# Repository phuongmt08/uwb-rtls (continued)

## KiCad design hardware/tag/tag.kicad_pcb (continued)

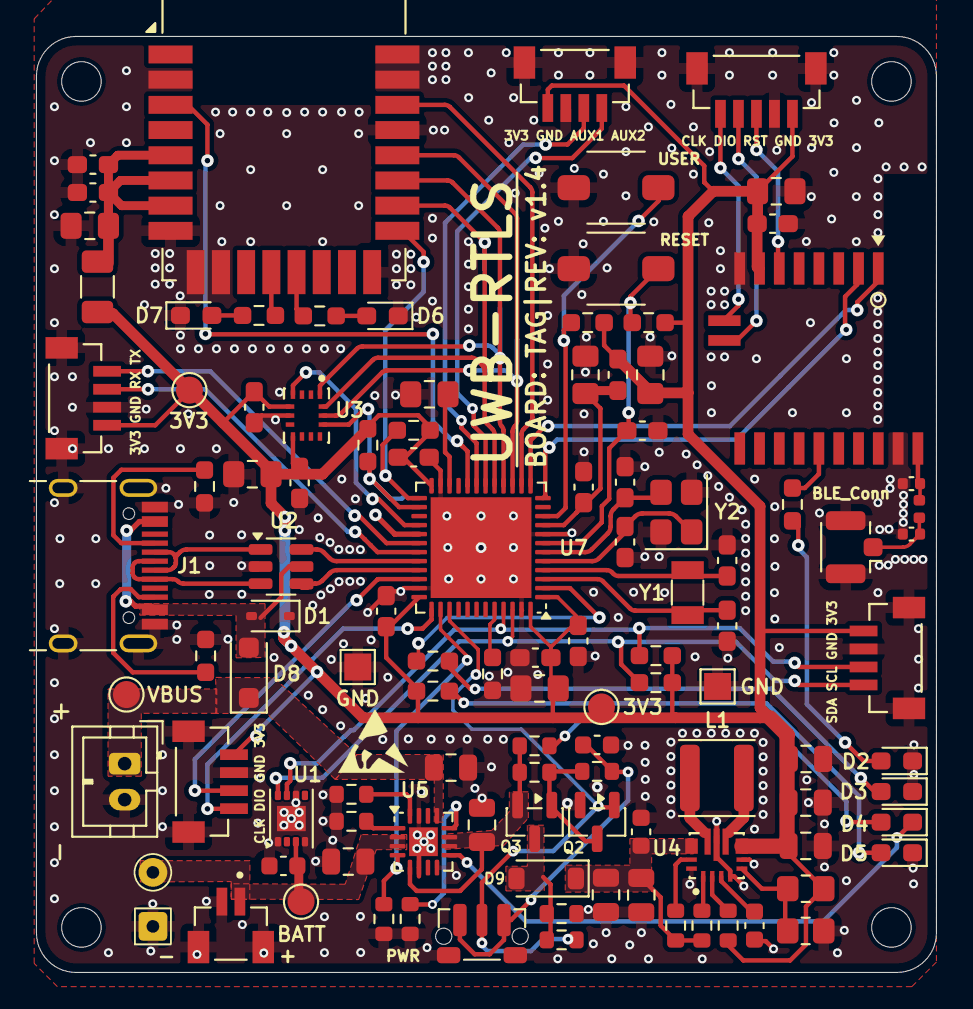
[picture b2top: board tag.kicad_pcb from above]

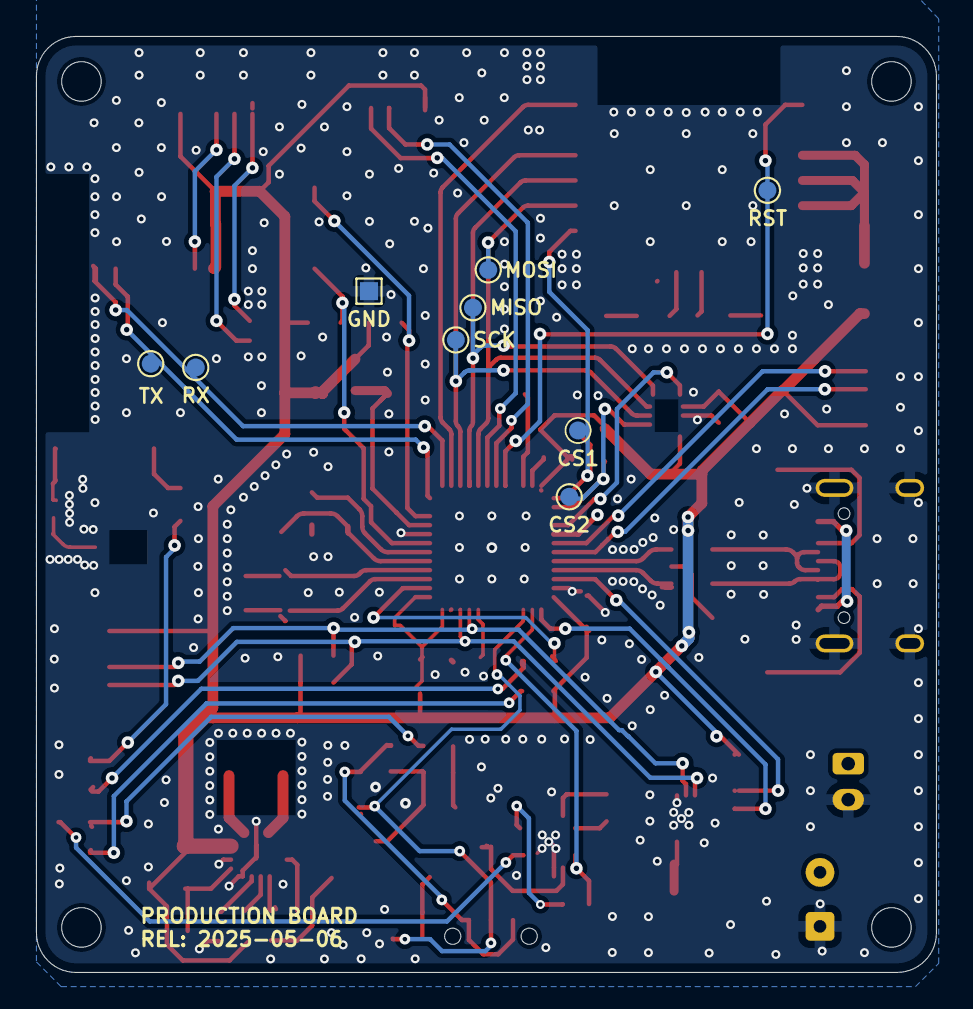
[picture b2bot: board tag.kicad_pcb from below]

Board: 2 copper layers, 50.0 x 52.0 mm, 121 parts (9 on the bottom side), 72 nets.

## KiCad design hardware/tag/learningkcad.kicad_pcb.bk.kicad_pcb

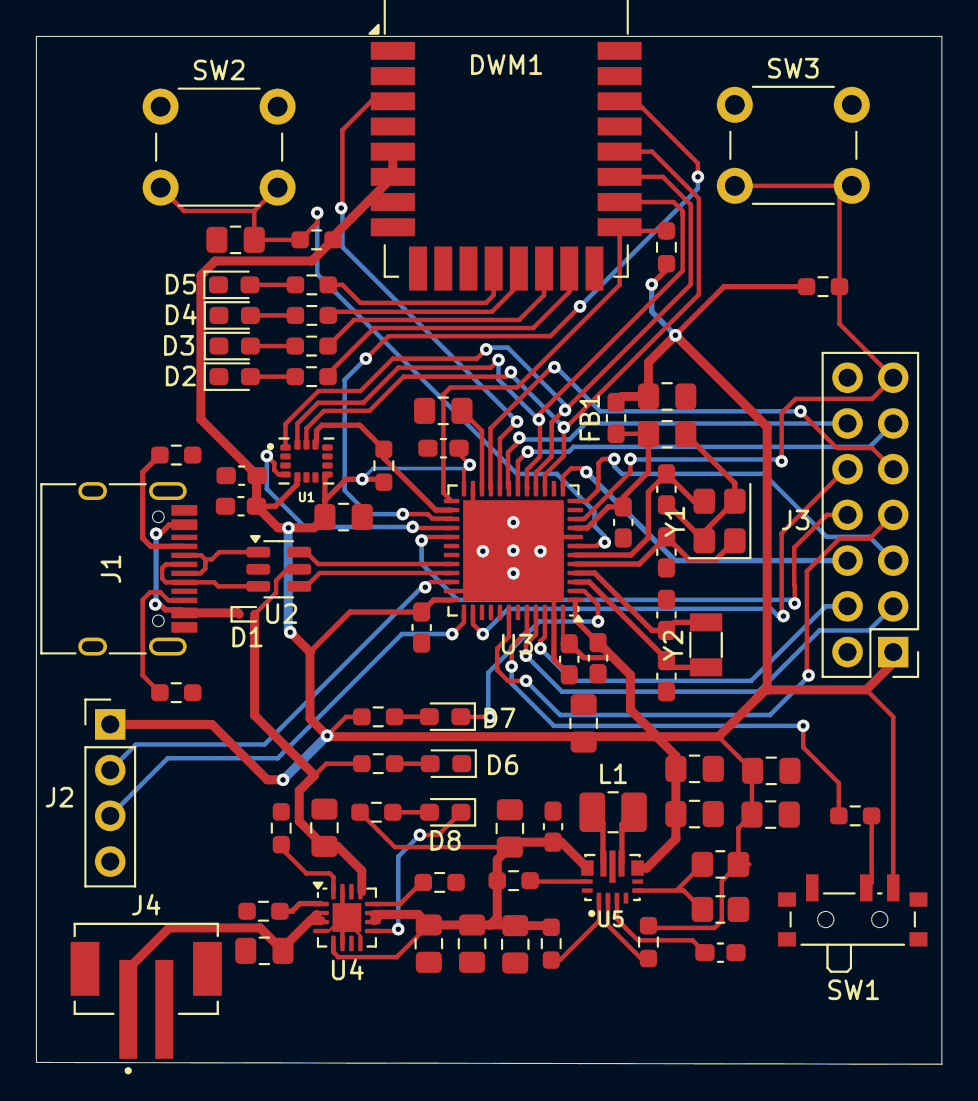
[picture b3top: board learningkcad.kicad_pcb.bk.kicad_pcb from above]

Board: 2 copper layers, 50.3 x 57.1 mm, 76 parts (0 on the bottom side), 65 nets.

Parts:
C1, C2, C5, C6, C7, C8, C9, C14, C18: 100n; C_0603_1608Metric_Pad1.08x0.95mm_HandSolder
C3, C13: 2.2u; C_0805_2012Metric_Pad1.18x1.45mm_HandSolder
C4, C15, C16, C17, C19: 10u; C_0805_2012Metric_Pad1.18x1.45mm_HandSolder
C10, C11, C23: 1u; C_0805_2012Metric_Pad1.18x1.45mm_HandSolder
C12: 100n; C_0805_2012Metric_Pad1.18x1.45mm_HandSolder
C20, C21, C22: 22u; C_0805_2012Metric_Pad1.18x1.45mm_HandSolder
C24, C25: 4.7u; C_0805_2012Metric_Pad1.18x1.45mm_HandSolder
CY1, CY2: 10p; C_0603_1608Metric_Pad1.08x0.95mm_HandSolder
CY3, CY4: 22p; C_0603_1608Metric_Pad1.08x0.95mm_HandSolder
D1: ESD9B5.0ST5G; D_SOD-923
D2, D3, D4, D5, D6, D7: LED; LED_0603_1608Metric_Pad1.05x0.95mm_HandSolder
D8: R; LED_0603_1608Metric_Pad1.05x0.95mm_HandSolder
DWM1: DWM1000
FB1: FerriteBead; L_0603_1608Metric_Pad1.05x0.95mm_HandSolder
J1: USB_C_Receptacle_USB2.0_16P; USB_C_Receptacle_HRO_TYPE-C-31-M-12
J2: Conn_01x04_Pin; PinHeader_1x04_P2.54mm_Vertical
J3: Conn_02x07_Odd_Even; PinHeader_2x07_P2.54mm_Vertical
J4: BATTERY; JST_B2B-PH-SM4-TB
L1: 1.5u; L_1008_2520Metric_Pad1.43x2.20mm_HandSolder
R1, R2, R7, R8, R9, R10, R14, R16, R17, R18: 10k; R_0603_1608Metric_Pad0.98x0.95mm_HandSolder
R3, R4, R11: 10K; R_0603_1608Metric_Pad0.98x0.95mm_HandSolder
R5, R6: 5k1; R_0603_1608Metric_Pad0.98x0.95mm_HandSolder
R12, R13: 4.7k; R_0603_1608Metric_Pad0.98x0.95mm_HandSolder
R15: 1.5k; R_0603_1608Metric_Pad0.98x0.95mm_HandSolder
R19: 3.1k; R_0603_1608Metric_Pad0.98x0.95mm_HandSolder
R20: 3.56k; R_0603_1608Metric_Pad0.98x0.95mm_HandSolder
R21: 470k; R_0805_2012Metric_Pad1.20x1.40mm_HandSolder
R22: 150k; R_0805_2012Metric_Pad1.20x1.40mm_HandSolder
SW1: SW_SPDT; SW_SPDT_PCM12
SW2, SW3: SW_Push; SW_PUSH_6mm_H9.5mm
U1: ICM-42688-P; PQFN50P300X250X97-14N
U2: USBLC6-2SC6 (DNP); SOT-23-6
U3: STM32F411CEUx; QFN-48-1EP_7x7mm_P0.5mm_EP5.6x5.6mm
U4: BQ24075RGT; VQFN-16-1EP_3x3mm_P0.5mm_EP1.6x1.6mm
U5: TPS63070RNMR; VREG_TPS63070RNMR
Y1: NX3225SA-24MHz; Crystal_SMD_3225-4Pin_3.2x2.5mm
Y2: NX3215SA-32.768kHz; Crystal_SMD_3215-2Pin_3.2x1.5mm

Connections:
+3.3V: C1.1, C2.1, C3.1, C4.1, C5.1, C6.1, C7.1, C8.1, C11.1, C19.1, C20.1, C21.1, C22.1, DWM1.5 (VDDAON), DWM1.6 (VDD3V3), DWM1.7 (VDD3V3), FB1.2, J2.1, J3.1, R1.1, R2.1, R3.2, R11.2, R13.2, R17.2, R21.1, SW1.3 (C), U1.5 (VDDIO), U1.8 (VDD), U3.1 (VBAT), U3.24 (VDD), U3.36 (VDD), U3.48 (VDD), U5.7_8 (VOUT)
+3.3VA: C9.1, C10.1, FB1.1, U3.9 (VDDA)
+BATT: C24.1, J4.1, U4.2 (BAT), U4.3 (BAT)
/FB: R21.2, R22.1, U5.5 (FB)
/IMU_INT: U1.4 (INT1/INT), U3.28 (PB15)
/LED_USR: D7.1 (K), U3.2 (PC13)
/PA0/BTN_USR: J3.13, R11.1, SW3.2, U3.10 (PA0)
/PA2 / USART2_TX: J3.5, U3.12 (PA2)
/PA3 / USART2_RX: J3.6, U3.13 (PA3)
/PA8 / TIM1_CH1: J3.8, U3.29 (PA8)
/PA15 / TIM2_CH1: J3.10, U3.38 (PA15)
/PB0 / ADC_IN8: J3.11, U3.18 (PB0)
/PB1 / ADC_IN9: J3.12, U3.19 (PB1)
/PB6 / TIM4_CH1: J3.7, U3.42 (PB6)
/PB8 / I2C1_SCL: J3.3, U3.45 (PB8)
/PB9 / I2C1_SDA: J3.4, U3.46 (PB9)
/PB10 / TIM2_CH3: J3.9, U3.21 (PB10)
/SPI_CS1: DWM1.17 (~SPICS), R2.2, U3.25 (PB12)
/SPI_CS2: R1.2, U1.12 (AP_CS), U3.26 (PB13)
/SPI_MISO: DWM1.19 (SPIMISO), U1.1 (AP_SDO/AP_AD0), U3.16 (PA6)
/SPI_MOSI: DWM1.18 (SPIMOSI), U1.14 (AP_SDA/AP_SDIO/AP_SDI), U3.17 (PA7)
/SPI_SCK: DWM1.20 (SPICLK), U1.13 (AP_SCL/AP_SCLK), U3.15 (PA5)
/SWDCLK: J2.3, U3.37 (PA14)
/SWDIO: J2.2, U3.34 (PA13)
/SYS: C15.1, C16.1, C17.1, C18.1, C25.1, R15.1, R16.2, R18.2, U4.5 (EN2), U4.10 (OUT), U4.11 (OUT), U5.12_13 (VIN)
/USB_OTG_DM: U2.6 (I/O1), U3.32 (PA11)
/USB_OTG_DP: U2.4 (I/O2), U3.33 (PA12)
/UWB_IQR: DWM1.22 (IRQ/GPIO8), U3.27 (PB14)
/UWB_LED_RX: DWM1.13 (GPIO2/RXLED), R9.2
/UWB_LED_RXOK: DWM1.15 (GPIO0/RXOKLED), R7.2
/UWB_LED_SDF: DWM1.14 (GPIO1/SFDLED), R8.2
/UWB_LED_TX: DWM1.12 (GPIO3/TXLED), R10.2
/UWB_RST: DWM1.3 (~RST), U3.20 (PB2)
GND: C1.2, C2.2, C3.2, C4.2, C5.2, C6.2, C7.2, C8.2, C9.2, C10.2, C11.2, C12.2, C13.2, C14.2, C15.2, C16.2, C17.2, C18.2, C19.2, C20.2, C21.2, C22.2, C23.1, C24.2, C25.2, CY1.1, CY2.1, CY3.1, CY4.1, D2.1 (K), D3.1 (K), D4.1 (K), D5.1 (K), D6.1 (K), DWM1.2 (WAKEUP), DWM1.8 (VSS), DWM1.9 (GPIO6/EXTRXE/SPIHA), DWM1.10 (GPIO5/EXTTXE/SPIPOL), DWM1.16 (VSS), DWM1.21 (VSS), DWM1.23 (VSS), DWM1.24 (VSS), J1.A1 (GND), J1.A12 (GND), J1.B1 (GND), J1.B12 (GND), J1.S1 (SHIELD), J2.4, J3.2, J3.14, J4.2, R5.1, R6.1, R14.1, R19.2, R20.2, R22.2, SW1.1 (A), SW2.1, SW3.1, U1.6 (GND), U1.7 (RESV_7), U1.11 (RESV_11), U2.2 (GND), U3.8 (VSSA), U3.23 (VSS), U3.35 (VSS), U3.47 (VSS), U3.49 (VSS), U4.4 (~CE), U4.6 (EN1), U4.8 (VSS), U4.15 (SYSOFF), U4.17 (VSS), U5.4 (GND), U5.6 (FB2), U5.10 (PGND), U5.15 (VSEL), Y1.2, Y1.4
unnamed: D1.1 (A1), J1.A4 (VBUS), J1.A9 (VBUS), J1.B4 (VBUS), J1.B9 (VBUS)
unnamed: D2.2 (A), R7.1
unnamed: D3.2 (A), R8.1
unnamed: D4.2 (A), R9.1
unnamed: D5.2 (A), R10.1
unnamed: D6.2 (A), R12.1
unnamed: D7.2 (A), R13.1
unnamed: D8.2 (A), R15.2
unnamed: D8.1 (K), U4.9 (~CHG)
unnamed: J1.A5 (CC1), R5.2
unnamed: J1.B5 (CC2), R6.2
unnamed: J1.A6 (D+), J1.B6 (D+), U2.3 (I/O2)
unnamed: J1.A7 (D-), J1.B7 (D-), U2.1 (I/O1)
unnamed: R4.1, SW1.2 (B)
unnamed: R4.2, U3.44 (BOOT0)
unnamed: C12.1, R3.1, SW2.2, U3.7 (NRST)
unnamed: CY3.2, U3.3 (PC14), Y2.2
unnamed: CY4.2, U3.4 (PC15), Y2.1
unnamed: CY1.2, U3.5 (PH0), Y1.1
unnamed: CY2.2, U3.6 (PH1), Y1.3
unnamed: C13.1, U3.22 (VCAP1)
unnamed: R19.1, U4.12 (ILIM)
unnamed: R20.1, U4.16 (ISET)
unnamed: R14.2, U4.1 (TS)
unnamed: R16.1, U5.14 (EN)
unnamed: L1.2, U5.11 (L1)
unnamed: L1.1, U5.9 (L2)
unnamed: R17.1, U5.2 (PG)
unnamed: R18.1, U5.1 (PS/SYNC)
unnamed: C14.1, U5.3 (VAUX)
VBUS: C23.2, D1.2 (A2), R12.2, U2.5 (VBUS), U4.13 (IN)

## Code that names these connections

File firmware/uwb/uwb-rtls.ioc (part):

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Mcu.Name=STM32F411C(C-E)Ux
Mcu.Package=UFQFPN48
Mcu.UserName=STM32F411CEUx
PA0-WKUP.GPIOParameters=GPIO_Label,GPIO_ModeDefaultEXTI
PA0-WKUP.GPIO_Label=BTN_USR
PA0-WKUP.GPIO_ModeDefaultEXTI=GPIO_MODE_IT_FALLING
PA0-WKUP.Signal=GPXTI0
PA10.Mode=Asynchronous
PA10.Signal=USART1_RX
PA11.Mode=Device_Only
PA11.Signal=USB_OTG_FS_DM
PA12.Mode=Device_Only
PA12.Signal=USB_OTG_FS_DP
PA13.Mode=Serial_Wire
PA13.Signal=SYS_JTMS-SWDIO
PA14.Mode=Serial_Wire
PA14.Signal=SYS_JTCK-SWCLK
PA2.GPIOParameters=GPIO_Label
PA2.GPIO_Label=UART2_BLE_TX
PA2.Mode=Asynchronous
PA2.Signal=USART2_TX
PA3.GPIOParameters=GPIO_Label
PA3.GPIO_Label=UART2_BLE_RX
PA3.Mode=Asynchronous
PA3.Signal=USART2_RX
PA4.GPIOParameters=GPIO_Label,GPIO_ModeDefaultEXTI
PA4.GPIO_Label=UWB_IRQ
PA4.GPIO_ModeDefaultEXTI=GPIO_MODE_IT_RISING
PA4.Signal=GPXTI4
PA5.Mode=Full_Duplex_Master
PA5.Signal=SPI1_SCK
PA6.Mode=Full_Duplex_Master
PA6.Signal=SPI1_MISO
PA7.Mode=Full_Duplex_Master
PA7.Signal=SPI1_MOSI
PA8.Signal=I2C3_SCL
PA9.Mode=Asynchronous
PA9.Signal=USART1_TX
PB0.GPIOParameters=GPIO_Label
PB0.GPIO_Label=AUX0
PB0.Signal=ADCx_IN8
PB1.GPIOParameters=GPIO_Label
PB1.GPIO_Label=AUX1
PB1.Signal=ADCx_IN9
PB12.GPIOParameters=GPIO_Speed,PinState,GPIO_PuPd,GPIO_Label
PB12.GPIO_Label=SPI1_CS1
PB12.GPIO_PuPd=GPIO_PULLUP
PB12.GPIO_Speed=GPIO_SPEED_FREQ_HIGH
PB12.PinState=GPIO_PIN_SET
PB12.Signal=GPIO_Output
PB13.GPIOParameters=GPIO_Speed,PinState,GPIO_Label
PB13.GPIO_Label=SPI1_CS2
PB13.GPIO_Speed=GPIO_SPEED_FREQ_HIGH
PB13.PinState=GPIO_PIN_SET
PB13.Signal=GPIO_Output
PB15.GPIOParameters=GPIO_Label
PB15.GPIO_Label=IMU_IRQ
PB15.Signal=GPXTI15
PB2.GPIOParameters=GPIO_PuPd,GPIO_Label
PB2.GPIO_Label=UWB_RST
PB2.GPIO_PuPd=GPIO_NOPULL
PB2.Signal=GPIO_Input
PB3.GPIOParameters=GPIO_PuPd,GPIO_Label
PB3.GPIO_Label=CHARGE_EN
PB3.GPIO_PuPd=GPIO_NOPULL
PB3.Signal=GPIO_Output
PB4.Signal=I2C3_SDA
PB5.GPIOParameters=GPIO_Label,GPIO_ModeDefaultEXTI
PB5.GPIO_Label=DIP1
PB5.GPIO_ModeDefaultEXTI=GPIO_MODE_IT_FALLING
PB5.Signal=GPXTI5
PB6.GPIOParameters=GPIO_Label,GPIO_ModeDefaultEXTI
PB6.GPIO_Label=DIP2
PB6.GPIO_ModeDefaultEXTI=GPIO_MODE_IT_FALLING
PB6.Signal=GPXTI6
PB7.GPIOParameters=GPIO_Label,GPIO_ModeDefaultEXTI
PB7.GPIO_Label=DIP3
PB7.GPIO_ModeDefaultEXTI=GPIO_MODE_IT_FALLING
PB7.Signal=GPXTI7
PB8.Mode=I2C
PB8.Signal=I2C1_SCL
PB9.Mode=I2C
PB9.Signal=I2C1_SDA
PC13-ANTI_TAMP.GPIOParameters=GPIO_Label
PC13-ANTI_TAMP.GPIO_Label=LED_USR
PC13-ANTI_TAMP.Signal=GPIO_Output
PC14-OSC32_IN.Signal=RCC_OSC32_IN
PC15-OSC32_OUT.Signal=RCC_OSC32_OUT
PH0\ -\ OSC_IN.Mode=HSE-External-Oscillator
PH0\ -\ OSC_IN.Signal=RCC_OSC_IN
PH1\ -\ OSC_OUT.Mode=HSE-External-Oscillator
PH1\ -\ OSC_OUT.Signal=RCC_OSC_OUT
RCC.HSE_VALUE=12000000
RCC.SYSCLKFreq_VALUE=96000000
RCC.SYSCLKSource=RCC_SYSCLKSOURCE_PLLCLK
board=custom

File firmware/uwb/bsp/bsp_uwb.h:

/**
 * @file       bsp_uwb.h
 * @copyright
 * @license
 * @version    0.4.0
 * @date       2025-12-11
 * @author     Phuong Mai
 * @brief      Board Support Package for UWB (DW1000)
 * @note       None
 * @example    None
 */
#ifndef __BSP_UWB_H
#define __BSP_UWB_H

/* Includes ----------------------------------------------------------- */
#include "common.h"
#include <stdbool.h>
#include "protos/protocol.pb.h"
#include "config.h"

#include "main.h"

typedef struct {
    uint16_t fp_amp1;
    uint16_t fp_amp2;
    uint16_t fp_amp3;
    uint16_t std_noise;
    uint16_t lde_threshold;
    uint16_t rx_pream_count;
    uint16_t fp_amp_norm_q8;
    uint16_t fp_snr_q8;
    uint16_t first_path_index_q6;
    uint16_t peak_path_index;
    uint16_t peak_path_amp;
    uint8_t  fp_confidence_q8;
    bool     confidence_valid;
    bool     valid;
} bsp_uwb_rx_quality_t;

typedef enum {
    BSP_UWB_EVENT_NONE = 0,
    BSP_UWB_EVENT_RX_OK,
    BSP_UWB_EVENT_RX_TIMEOUT,
    BSP_UWB_EVENT_RX_ERROR,
    BSP_UWB_EVENT_TX_DONE
} bsp_uwb_event_type_t;

typedef struct {
    bsp_uwb_event_type_t type;
    bool                 rx_windowed;
    uint16_t             rx_len;
    uint8_t              rx_data[128];
    uint64_t             rx_ts;
    uint64_t             tx_ts;
    bsp_uwb_rx_quality_t rx_quality;
} bsp_uwb_event_t;

/* Pin definitions (based on BU01 schematic) ------------------------- */
/* SPI pins - connected to SPI1 peripheral */
#define UWB_SPI_PORT        GPIOA
#define UWB_SCK_PIN         GPIO_PIN_5   /* PA5 - SPICLK (Pin 20) */
#define UWB_MISO_PIN        GPIO_PIN_6   /* PA6 - SPIMISO (Pin 19) */
#define UWB_MOSI_PIN        GPIO_PIN_7   /* PA7 - SPIMOSI (Pin 18) */
#ifdef UWB_CS_PORT
#undef UWB_CS_PORT
#endif
#ifdef UWB_CS_PIN
#undef UWB_CS_PIN
#endif
#define UWB_CS_PORT         SPI1_CS1_GPIO_Port
#define UWB_CS_PIN          SPI1_CS1_Pin  /* PB12 - SPICS (Pin 17) */

/* Control pins */
#ifdef UWB_RST_PORT
#undef UWB_RST_PORT
#endif
#ifdef UWB_RST_PIN
#undef UWB_RST_PIN
#endif
#define UWB_RST_PORT        UWB_RST_GPIO_Port
#define UWB_RST_PIN         UWB_RST_Pin   /* PB2 - RST (Pin 3) */
#define UWB_IRQ_PORT        UWB_IRQ_GPIO_Port
#define UWB_IRQ_PIN         UWB_IRQ_Pin   /* PA4 - IRQ/GPIO8 (Pin 22) */

/* Note: RX/TX LEDs are controlled by DW1000 GPIO2/GPIO3 directly, not STM32 */

/* Public function prototypes ----------------------------------------- */
/**
 * @brief Initialize DW1000 device
 * @return BSP_OK on success, BSP_ERR on failure
 */
bsp_err_t bsp_uwb_init(void);

/**
 * @brief  Check if UWB driver was successfully initialized.
 * @retval true if initialized, false otherwise
 */
bool bsp_uwb_is_initialized(void);

/**
 * @brief Configure UWB radio parameters from protobuf UWB config.
 * @param[in] cfg  Pointer to protobuf_uwb_cfg_t (sys_config.uwb)
 * @return BSP_OK on success, BSP_ERR on failure
 */
bsp_err_t bsp_uwb_configure(const protobuf_uwb_cfg_t *cfg);

/**
 * @brief Transmit a frame (blocking until complete)
 * @param[in] data   Frame data
 * @param[in] length Frame length in bytes
 * @return BSP_OK on success, BSP_ERR on failure
 */
bsp_err_t bsp_uwb_tx(const void *data, uint16_t length);

/**
 * @brief Non-blocking RX check - returns immediately
 * @param[out] data    Receive buffer
 * @param[in]  length  Maximum buffer size
 * @param[out] out_len Actual received length
 * @return BSP_OK if frame received, BSP_ERR if no frame or error
 * @note This function does NOT block. Returns immediately with status.
 */
bsp_err_t bsp_uwb_rx(void *data, uint16_t length, uint16_t *out_len);

/**
 * @brief Read 40-bit timestamp from DW1000 register
 * @param[in]  reg_addr  Register address (e.g., 0x15 for RX, 0x17 for TX)
 * @param[in]  sub_addr  Sub-address (usually 0x00)
 * @param[out] timestamp Pointer to store 64-bit value (40-bit in LSBs)
 * @return BSP_OK on success, BSP_ERR on failure
 */
bsp_err_t bsp_uwb_read_40bit(uint8_t reg_addr, uint8_t sub_addr, uint64_t *timestamp);

/**
 * @brief Control hardware reset pin
 * @param[in] active  true = assert reset, false = deassert
 */
void bsp_uwb_reset(bool active);

/**
 * @brief Enable RX with specific timeout
 * @param[in] timeout_ms Timeout in milliseconds (0 = continuous)
 * @return BSP_OK on success, BSP_ERR on failure
 */
bsp_err_t bsp_uwb_enable_rx(uint32_t timeout_ms);

/**
 * @brief Enable RX delayed
 * @param[in] rx_timestamp_dw 40-bit DW1000 timestamp when to start receiving
 * @param[in] timeout_ms Timeout in milliseconds
 * @return BSP_OK on success, BSP_ERR on failure
 */
bsp_err_t bsp_uwb_enable_rx_delayed(uint64_t rx_timestamp_dw, uint32_t timeout_ms);

/**
 * @brief Force DW1000 to idle state (turn off TX/RX)
 * @note Call this when stopping ranging to turn off RX/TX LEDs
 */
void bsp_uwb_idle(void);

/**
 * @brief Put DW1000 into low-power sleep.
 * @note Intended for long standby gaps only. Hot ranging paths should keep
 *       using bsp_uwb_idle() so TX/RX timing is not disturbed.
 */
bsp_err_t bsp_uwb_sleep_enter(void);

/**
 * @brief Wake DW1000 from sleep using the SPI CS wake mechanism.
 */
bsp_err_t bsp_uwb_sleep_wake(void);

/**
 * @brief Return true when the BSP believes DW1000 is in sleep mode.
 */
bool bsp_uwb_is_sleeping(void);

/**
 * @brief Get cached first-path quality diagnostics of the last RX frame.
 * @param[out] quality Output quality metrics.
 * @return BSP_OK when valid diagnostics are available.
 */
bsp_err_t bsp_uwb_get_last_rx_quality(bsp_uwb_rx_quality_t *quality);

/**
 * @brief Get cached RX timestamp of the last successfully received frame.
 * @param[out] timestamp 40-bit timestamp in DW units.
 * @return BSP_OK on success, BSP_ERR if unavailable.
 */
bsp_err_t bsp_uwb_get_last_rx_timestamp(uint64_t *timestamp);

/**
 * @brief Get cached TX timestamp of the last completed TX frame.
 * @param[out] timestamp 40-bit timestamp in DW units.
 * @return BSP_OK on success, BSP_ERR if unavailable.
 */
bsp_err_t bsp_uwb_get_last_tx_timestamp(uint64_t *timestamp);

/**
 * @brief Get configured TX antenna delay
 * @return TX antenna delay in DW1000 time units
 */
uint16_t bsp_uwb_get_tx_antenna_delay(void);

/**
 * @brief Transmit frame at specific delayed time (scheduled TX)
 * @param[in] data Frame data
 * @param[in] length Frame length in bytes
 * @param[in] tx_timestamp 40-bit DW1000 timestamp when to transmit
 * @return BSP_OK on success, BSP_ERR on failure
 * @note Uses DW1000 delayed TX feature to transmit at precise time
 */
bsp_err_t bsp_uwb_tx_delayed(const void *data, uint16_t length, uint64_t tx_timestamp);
bool bsp_uwb_is_rx_ready(void);
uint64_t bsp_uwb_get_current_time_dw(void);
bsp_err_t bsp_uwb_validate_delayed_tx(uint64_t tx_timestamp_dw, uint64_t min_guard_dw);
uint16_t bsp_uwb_get_rx_antenna_delay(void);
float bsp_uwb_get_range_bias(float range_raw_m);


void bsp_uwb_get_rx_error_counts(uint32_t *timeout,
                                 uint32_t *crc_err,
                                 uint32_t *phr_err,
                                 uint32_t *sync_err);
void bsp_uwb_reset_rx_error_counts(void);

/**
 * @brief Notify BSP about UWB IRQ edge (call from EXTI callback)
 */
void bsp_uwb_on_irq(void);
void bsp_uwb_dwt_isr(void);

/**
 * @brief Clear pending UWB IRQ event flag
 */
void bsp_uwb_clear_irq_event(void);

/**
 * @brief Wait for UWB IRQ event flag with timeout
 * @param[in] timeout_ms Timeout in milliseconds
 * @return true if IRQ event occurred, false on timeout
 */
bool bsp_uwb_wait_for_irq_event(uint32_t timeout_ms);

typedef struct
{
  uint32_t tx_done;
  uint32_t rx_ok;
  uint32_t queue_overflow;
  uint32_t irq_extra_pass;
  uint32_t rx_rearm_fail;
} bsp_uwb_event_stats_t;

/**
 * @brief Fetch the latest event generated by the UWB ISR.
 * @param[out] out_event Pointer to destination struct
 * @return true if a new event was copied, false if no event.
 */
bool bsp_uwb_get_event(bsp_uwb_event_t *out_event);

/**
 * @brief Read and clear event-driven ISR diagnostics.
 */
void bsp_uwb_get_event_stats(bsp_uwb_event_stats_t *stats);

/**
 * @brief Discard any pending UWB events
 */
void bsp_uwb_clear_event(void);

/**
 * @brief Read internal temperature and voltage of DW1000 chip.
 * @param[out] temp  Pointer to float to store temperature in C.
 * @param[out] vbat  Pointer to float to store battery voltage in V.
 * @return BSP_OK on success, BSP_ERR on failure.
 */
bsp_err_t bsp_uwb_read_temp_vbat(float *temp, float *vbat);

#endif /* __BSP_UWB_H */
/* End of file -------------------------------------------------------- */

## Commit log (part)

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2026-05-06 wip hardware changes
2026-05-06 feat: release final final hardware for tag + anchor
2026-05-10 update: adjust TDMA timing parameters for 4-anchors ranging
2026-05-10 update: modify DIP switch handling
2026-05-11 refactor: update configuration parameters
2026-05-11 refactor: update UWB and filtering logic
2026-05-11 feat: add UWB data recorder
2026-05-11 wip minor changes
2026-05-11 update: track last selected anchors mask in ranging results
2026-05-11 feat: implement end session packet sending
2026-05-12 feat: refactor calibration logic to use gradient descent approach
2026-05-12 refactor: sys_logger functions for RAM-based logging
2026-05-12 update: UWB configuration parameters and enable smart power
2026-05-12 update: correct name functions to resolve build errors
2026-05-12 feat: Enhance UWB firmware with Mahalanobis pre-filtering and quality metrics
2026-05-13 feat: Implement target anchor calibration mode
2026-05-14 feat: add simulation for prefilter logic
2026-05-14 feat: remove tag auto calibration logic
2026-05-15 feat: remove preset case logging from app_tag_init function
2026-05-15 update: rebuild protocol message
2026-05-15 feat: modular simulation with web workers, auto-server, and visual dashboard
2026-05-15 update: improve svg thumbnail in dashboard
2026-05-15 update: add data log files to .gitignore
2026-05-16 fix: update sector erase functions
2026-05-16 update: UWB firmware configuration
2026-05-17 feat(ble): enhance BLE communication with TX/RX activity indicators and address handling
2026-05-17 update: adjust tag and anchor height
2026-05-17 update: default destination addresses in FOTA tests
2026-05-17 feat: implement automatic central dongle detection and finalize FOTA logic
2026-05-17 update: improve BLE advertising logic and fix UART read function
2026-05-18 update gitignore (txt, csv file)
2026-05-18 feat(icm42688): - add hardware offset reset API - fix init calibration flow to avoid double bias compensation - remove redundant gravity compensation
2026-05-18 chore(ibsp_mu): - change IMU config (gyro, accel FS) - disable use calib data - add null pointer validation
2026-05-18 fusion log data
2026-05-18 feat(simulation): simulate and plot ukf data
2026-05-18 update: change UART baud rate to 460800
2026-05-18 refactor sys_sensor_fusion - change define - add comment - track error
2026-05-18 update: enhance DFU and FOTA, and fix various issues
2026-05-19 feat: add pad support and bottom case housing for anchor
2026-05-19 update: enhance versioning system
2026-05-19 Resolve conflicts, update protocol files, and optimize anchor calibration solver
2026-05-19 feat: update clock to 96MHz, configure UART DMA, and sync idle-line logic
2026-05-19 feat: integrate max17048 battery bsp and system power management
2026-05-20 (html) change direct to relative path
2026-05-20 (simulation/live_plot) add ground truth for graph_d
2026-05-21 feat: implement smart discovery and tracking modes for polling mode
2026-05-21 feat: remove screen mount, add UWB air vents and adjust LED of enclosure tag
2026-05-21 refactor: time-optimize ranging logic
2026-05-22 (live_plot): fix comm error
2026-05-22 (simulation) test ukf with float32 and ukf logic like c
2026-05-22 (live_plot) update ui
2026-05-22 (simulation) refactor code
2026-05-22 (main.c): refactor code
2026-05-22 feat: stream UKF fusion frames from predict task
2026-05-22 (uwb_gateway): parse STM fusion UART frames
2026-05-22 (simulation): add requirement, update dashboard
2026-05-22 feat: initialization checks and error handling
2026-05-22 (main): update TEST_SEND_POS
2026-05-22 change config - tdma - position - sys
2026-05-22 fix(uwb_gateway)
2026-05-22 fix(module): write fp_amp_norm and fp_snr to csv
2026-05-22 refactor: update Mahalanobis pre-filter
2026-05-22 Update: schematic with new dimensions and additional notes
2026-05-23 update simulation_dashboard
2026-05-23 feat(simulation): - live_plot multi thread - update config
2026-05-23 feat(simulation) - live_plot: auto connect COM, enable quit app with Ctrl C - gui/gui_stm: enable quit app with Ctrl C - change config.py
2026-05-23 (exxcel) save antenna delay
2026-05-23 (programmer): add include arm_libs to Makefile
2026-05-23 (bsp_imu): refactor check err
2026-05-23 (bsp_io): change send by usb for test
2026-05-23 (main): add logic set device id for anchor
2026-05-23 refactor(mw_filter): discard first 10 samples in ukf_init_filter
2026-05-23 (sys_sensor_fusion): - change ukf value - change calculate/return yaw
2026-05-23 (simulation): - new python code to test fusion in mcu - change config
2026-05-23 refactor: enhance smart discovery and tracking logic
2026-05-24 fix: preserve DATA_STORAGE memory when erasing before flashing the new app
2026-05-24 chore: adjust timing parameters for improved performance
2026-05-24 feat: Improve FOTA controller logic and fix minor bugs
2026-05-24 refactor: migrate bare-metals to rtos-based
2026-05-24 feat: UWB and sensor fusion integration
2026-05-26 ci: add AI release notes workflow
2026-05-26 fix: add retry on 429 rate limit for Gemini API
2026-05-26 fix: use GitHub Models as primary AI provider
2026-05-26 fix: switch to Groq, remove Gemini retry logic
2026-05-27 refactor: remove unused Mahalanobis pre-filter history functions
2026-05-27 feat: optimize RX quality capture by directly querying DW1000 registers
2026-05-27 feat: update ranging logic for improved performance + correct logic prefilter in firmware
2026-05-27 feat: remove unused snr penalty
2026-05-27 Add SEGGER SystemView FreeRTOS tracing
2026-05-28 feat: enable stack start retrieval for FreeRTOS tasks
2026-05-29 change config version and simulation config
2026-05-29 wip: - imu event-driven - stream to host
2026-05-29 (gui): gen log file
2026-05-29 - Move UKF Vx and UKF Vy from IMU Rotation plot to Integrated Velocity plot - Show current sample index in trajectory replay controls - Render replay breadcrumbs as points instead of connected lines 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
2026-05-31 refactor send fusion log
2026-05-31 update: migrate sensor fusion to rtos-based firmware
2026-05-31 refactor: complete housing geometry for Anchor and Tag boards; optimized for 3D printing
2026-06-02 wipppp
2026-06-02 fusion on mcu
2026-06-03 temp: save current commands and requirements
2026-06-03 feat: finalize studio integration and remove old gui
2026-06-04 update: Use multi-processsors build instead of single-processor build
2026-06-04 refactor: ram memory layout + rebuild protobuf message
2026-06-04 update: optimize flash size and add more uwb config fields to flash storage
2026-06-05 refactor: adjust UI device manager & live tracking, fix logic detect dongle
2026-06-07 refactor: send fusion log
2026-06-07 refactor: remove the duplicate logic on app_tag + optimize code for size
2026-06-08 (dashboard): record fusion frame
2026-06-08 feat: port UI from code python to XML designer
2026-06-09 call API update UI for device_manager tabs and fix some bug in software
2026-06-09 feat: implement broadcast logic for beacon and observer GAP roles
2026-06-09 update: move the front-end logic code from .py to .ui, update UI for log_tab
2026-06-10 fix: correct UI logic when parsing the "logs data" files
2026-06-10 Fix: BLE broadcast and central ADV test flow
2026-06-11 feat(simulation): add UKF prefilter GUI, simulation worker, and trajectory replay
2026-06-11 feat(protocol): add prefilter configuration and vehicle control/status messages
2026-06-11 feat(hw/mcu): configure ADC DMA conversion and skip IMU on non-tag devices
2026-06-11 feat(network): route VEHICLE packets to serial when active
2026-06-11 test(vv_testings): add device information get request in test_pushing_log
2026-06-11 test(vv_testings): improve command and calibration test output verification
2026-06-12 fix: remap BLE UART RX pin to P0.05 due to burned-out pin
2026-06-13 ble log: slow push
2026-06-13 - ble log fast push - add print debug in test_pushing_log - mcu auto send log
2026-06-14 refactor: move query state machine into app services layer
2026-06-15 wip: fusion stream
2026-06-15 refactor: restructure session/ranging/log workflow, normalize real data handling, add command bypass flags, and refine geofencing logic
2026-06-16 - implement stream log on supermini nrf52840 - test_ble_log: + scan by uuid + choose device to connect
2026-06-16 user can endsession and choose another device to get log by hotkey q
2026-06-16 send ack in poll
2026-06-16 cleanup: remove legacy uwb_gui_monitor files
2026-06-16 fix(sys_pm): rate-limit critical hardware alerts and PM warnings to 1s
2026-06-16 feat(app_anchor): remove auto-calibration preprocessor guards and update positioning config
2026-06-16 feat(hw): configure ADC DMA conversion and skip IMU on non-tag devices
2026-06-16 feat(config): support DEFAULT_ZONE_ID selection and static defaults for Zone 2
2026-06-17 wip: log data - peri: print seq of log packet - mcu: add variables to debug, fix not auto return true - app: remove auto start log when connect, only start when press Start Log
2026-06-17 wip: waiting_ack error
2026-06-17 change stream trajectory
2026-06-17 wip: app fusion stream
2026-06-18 feat(geofencing): add anchor authoring, map sync, room rename, 2.5D preview tuning, and layout read/write workflow
2026-06-19 feat(ble_bridge): gate peri rx stats and logs behind debug macro
2026-06-19 refactor(test_ble_log): adjust ACK retry, keepalive and scan settings
2026-06-19 feat(network): track transmission statistics and BLE packet counts
2026-06-19 refactor(network): update BLE adv config logging and tracker init
2026-06-19 config(ble_peripheral): change UART baudrate to 115200
2026-06-19 refactor(sys_ble): restructure peripheral advertisement configuration
2026-06-19 feat(ble_bridge): support debug stream logging and define peri rx variables
2026-06-19 refactor(network): remove network core and cmd log debug stats
2026-06-19 feat: add full library for requirements
2026-06-19 Refactor: geofence map persistence and config storage
2026-06-19 refactor: adjust library
2026-06-20 /* test anchor layout */ - freertos + fix mode disable fusion - config + change anchor to eco mode - live_plot + draw distance graph by dot
2026-06-20 /* fix log and stream */ - ble + remove handle ack + print status every 5s + increase buffer size to 1024 - mcu + reduce resend ack to 3s + reset s_log_tracker in endsession - scripts + log: disable 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
2026-06-20 - test send fusion log - disable ranging abort
2026-06-20 fix: error ble after merge
2026-06-20 update(geofence): adding more objects, improve user-friendliness
2026-06-22 disable read temp of imu to test
2026-06-24 feat: add logic call api rtos, set change interface usb/uart dev mode, logic ble params edit
2026-06-24 feat: implement sleeping logic during IDLE state for both STM32 and NRF +fix minor bugs
2026-06-25 feat: creat communication test tab, bonus macro app
2026-06-25 refactor: fix cant kill app, add message ble into tab communication/test
2026-06-25 refactor: fix logic send twice api in tab communication & fix address for app
2026-06-25 refactor: fix disconnect dongle cant open popup scan, format decode data, block send twice for packet
2026-06-25 simulation: - add 2 mode view data in graph d
2026-06-25 fix UWB Firmware
2026-06-25 refactor adv config set
2026-06-26 refactor: improve logic send packet, import address and auto-map tester destination
2026-06-26 feat: implement packet device_type_get/set && fix bug in tab log&communication, call battery information polling(2s)
2026-06-27 - uwb: send sensor fusion BLE/UART data with int16 x100 fields and anchor metadata - pi: accept the new fusion uart payload length and decode fixed-point values - dashboard: support the new fusion fr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
2026-06-27 refactor: change state button start/stop log and clear log, add logic button connect device other
2026-06-28 (test_fusion_stream): add hot key send ranging stop
2026-06-28 uwb: fix handler ranging stop
2026-06-29 feat: add helper scheduler for ranging & log, reflow record session
2026-06-30 feat: - packet handler for rtos_task_stats_get_t , rtos_resource_get_t, sensor_fusion_cfg_get_t, sys_config_set_t - force antenna delay - live plot: change graph_d x-axis to time
2026-06-30 feat(vv_testing): - send packet - provision otp
2026-06-30 refactor: change adv name
2026-06-30 feat: enable UWB sleep mode in discovery state when ECO mode is configured
